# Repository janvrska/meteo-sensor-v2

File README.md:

# Meteo sensor v2
## Custom PCB project of LoraWAN weather sensor

<div>

</div>

**Components :**
 - [Atmel ATMega3208](https://cz.mouser.com/ProductDetail/Microchip-Technology-Atmel/ATMEGA3208-AFR?qs=y6ZabgHbY%252ByqMua8ssBYRQ==) 
 - [Lora E5 SoC](https://cz.mouser.com/ProductDetail/Seeed-Studio/317990687?qs=hd1VzrDQEGhZOj13wvzSLA==)
 - [Sensirion SHT41](https://cz.mouser.com/ProductDetail/Sensirion/SHT41-AD1B-R2?qs=XAiT9M5g4x92rdly9nbdGg==)
 - [IPX connector](https://cz.mouser.com/ProductDetail/Amphenol-RF/A-1JB?qs=ncxkyCpAYDBidtvTkuzl1Q==)
 - 100 nF capacitors
 - 10 uF capacitors
 - 10k Ω resistors
 - 22 Ω resistors
 - pin headers for debugging, flashing

**Software:**
 - [MegaCoreX](https://github.com/MCUdude/MegaCoreX) - environment for Arduino compatibility  (Serial, Wire, Interrupts)
 - [Sensirion I2C SHT4X library](https://github.com/Sensirion/arduino-i2c-sht4x) -  SHT41 sensor data reading
 - [Platformio](https://platformio.org/)  - development, flashing ATMega

This project assumes, that credentials were configured by Serial [Lora E5 AT Commands](https://files.seeedstudio.com/products/317990687/res/LoRa-E5%20AT%20Command%20Specification_V1.0%20.pdf) (DevEUI, AppKey) before flashing the project code. 

**Flow:**
 1. Should be in a range of some nearest LoraWAN Gateway (can look on [TTNMapper](https://ttnmapper.org/))
 2. Power on the device with 3.3 V (2x AA or 2x AAA batteries) connected to VCC and GND pins (look at [board schema](https://github.com/janvrska/meteo-sensor-v2/blob/main/main-board/board.pdf), SV1 blue line GND down, red line VCC)
 3. The device will try to OTA join configured LoraWAN network
 4. Broadcast data packet (temperature, humidity, voltage)
 5. 2.5 minutes sleeping (configured for DR5, spread factor 7, make sure to not violate ETSI regulations or TTN fair access policy. Should be [calculated](https://avbentem.github.io/airtime-calculator/ttn/eu868) before use)
 6. Back to step 4.
 ```mermaid
stateDiagram
    [*] --> PowerOn
    PowerOn --> Join
    Join --> Measure
    Measure --> SendPacket
    SendPacket --> Sleep
    Sleep --> Measure
```
 
 **Low power** (250 µA measured in sleep)
 - use AT+DR=DR5 (will work only if a gateway is close or open area without a lot of RF noise)
 - use AT+POWER=2 (same above)
 - other AT commands already used in code

**TTN**

Use this payload [formatter](https://github.com/janvrska/meteo-sensor-v2/blob/main/ttn-payload-formatter.js) for decoding. Weather data can be later processed with some TTN integration options (MQTT, webhooks...) 

From personal testing, the sensor could transmit for 4 months on 2x AA batteries with default settings (DR5, AT+POWER=2)

**Photos of setup:**

Soldered by hand and hot air gun
<div>

</div>

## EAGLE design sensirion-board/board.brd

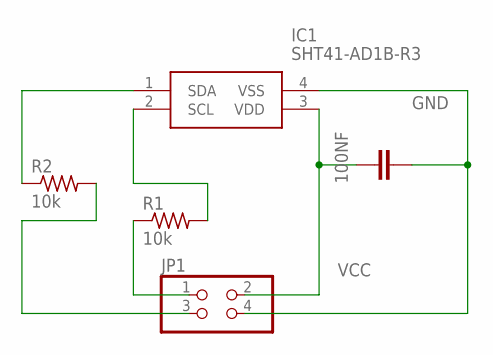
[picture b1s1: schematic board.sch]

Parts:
100NF: 100nF; CAP_0805
IC1: SHT41-AD1B-R3; SHT41AD1BR3
JP1: PINHD-2X2; 2X02
R1, R2: 10k; RES_0805

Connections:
GND: 100NF.2, IC1.4 (VSS), JP1.4
unnamed: JP1.3, R2.2
unnamed: IC1.2 (SCL), R1.2
unnamed: JP1.1, R1.1
unnamed: IC1.1 (SDA), R2.1
VCC: 100NF.1, IC1.3 (VDD), JP1.2

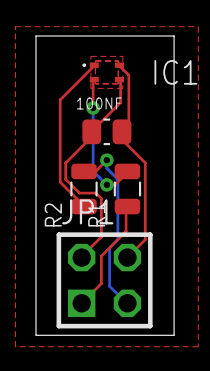
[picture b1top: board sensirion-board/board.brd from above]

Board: 2 copper layers, 7.7 x 16.6 mm, 5 parts (0 on the bottom side), 6 nets.

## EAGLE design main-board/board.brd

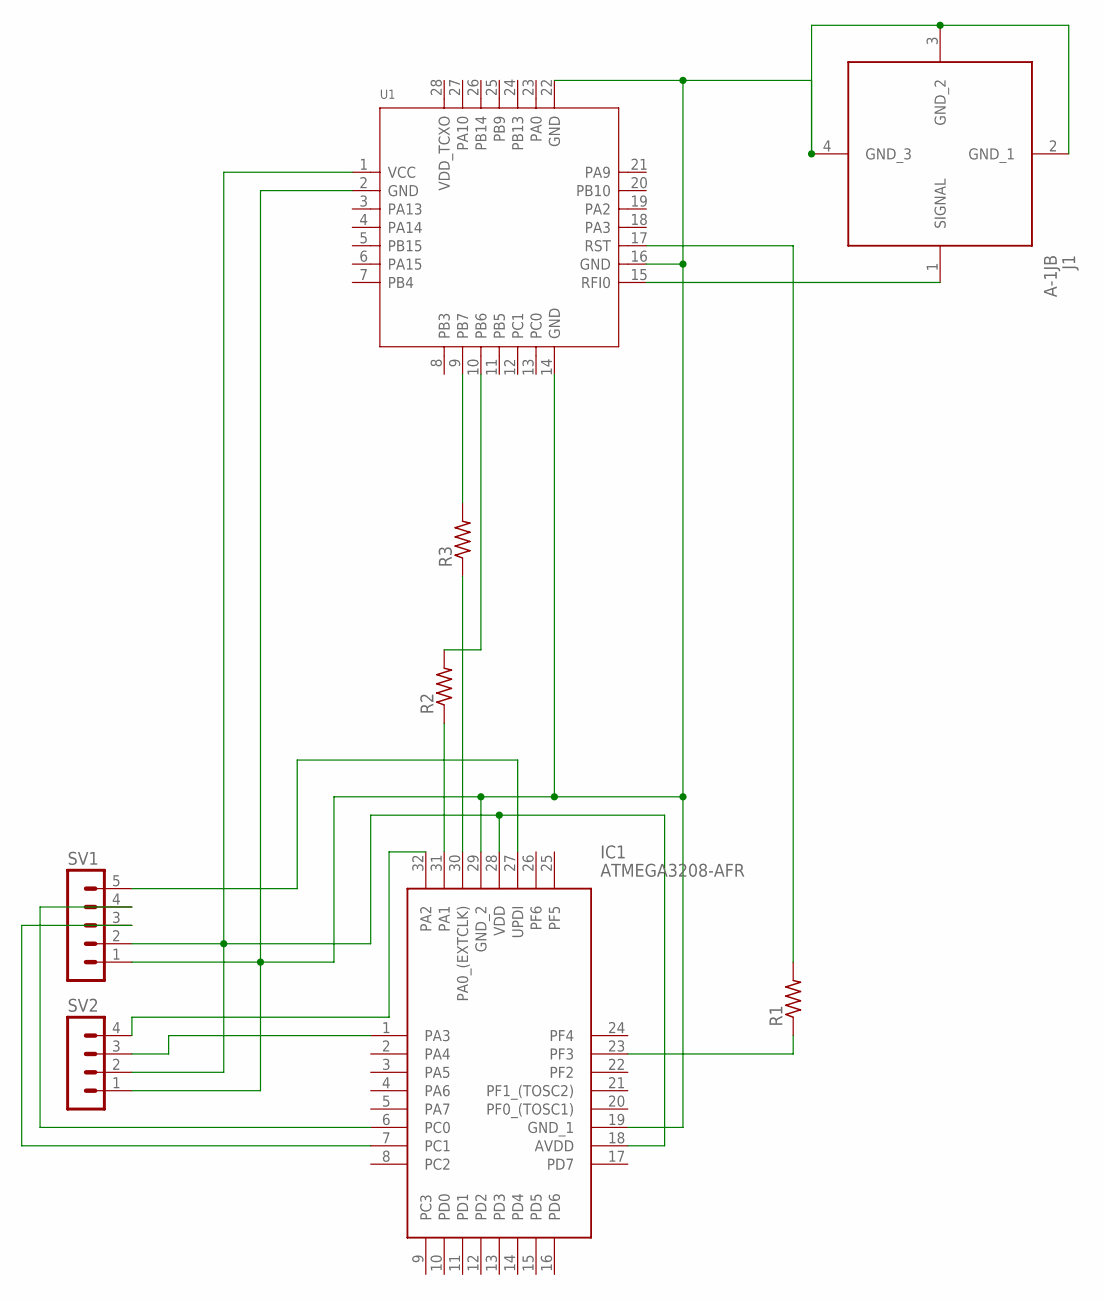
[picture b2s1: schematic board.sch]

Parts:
IC1: ATMEGA3208-AFR; QFP80P900X900X120-32N
J1: A-1JB; A1JB
R1, R2, R3: 22; RES_0805
SV1: MA05-1
SV2: MA04-1
U1: MODULE_LORA_E5; MODULE28P-1.25-12X12X2.5MM

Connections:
unnamed: IC1.19 (GND_1), IC1.29 (GND_2), J1.2 (GND_1), J1.3 (GND_2), J1.4 (GND_3), SV1.1, SV2.1, U1.2 (GND), U1.14 (GND), U1.16 (GND), U1.22 (GND)
unnamed: IC1.27 (UPDI), SV1.5
unnamed: IC1.18 (AVDD), IC1.28 (VDD), SV1.2, SV2.2, U1.1 (VCC)
unnamed: R1.2, U1.17 (RST)
unnamed: J1.1 (SIGNAL), U1.15 (RFI0)
unnamed: R3.2, U1.9 (PB7)
unnamed: R2.2, U1.10 (PB6)
unnamed: IC1.23 (PF3), R1.1
unnamed: IC1.31 (PA1), R2.1
unnamed: IC1.30 (PA0_(EXTCLK)), R3.1
unnamed: IC1.32 (PA2), SV2.4
unnamed: IC1.1 (PA3), SV2.3
unnamed: IC1.6 (PC0), SV1.4
unnamed: IC1.7 (PC1), SV1.3

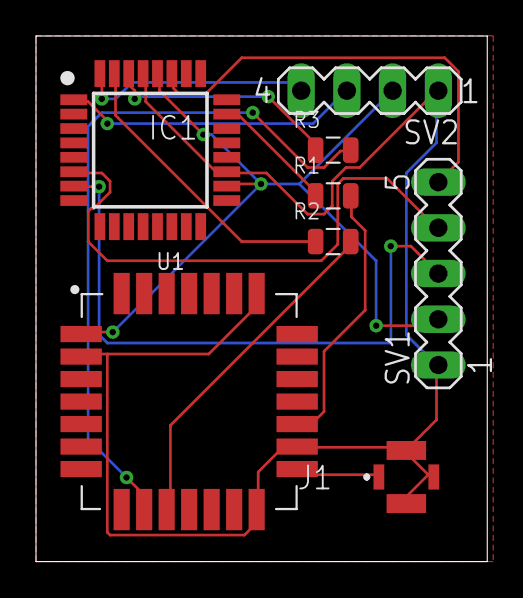
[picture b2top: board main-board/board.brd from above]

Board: 2 copper layers, 25.1 x 29.2 mm, 8 parts (0 on the bottom side), 14 nets.

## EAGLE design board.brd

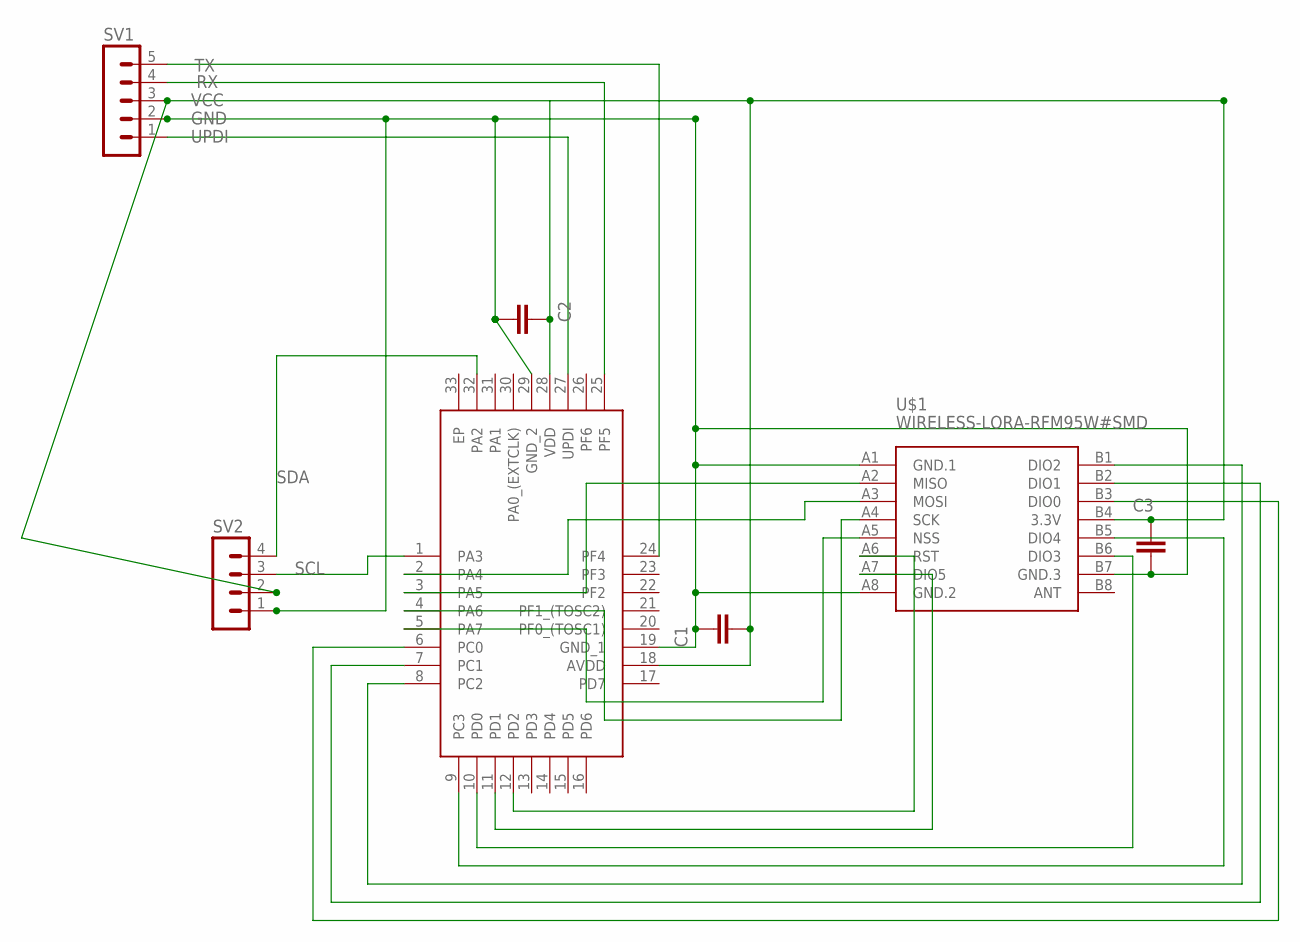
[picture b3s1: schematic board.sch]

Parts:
C1, C2, C3: CC0805KRX7R9BB104; CAP_0805
IC1: ATMEGA3208-MFR; QFN50P500X500X90-33N
SV1: MA05-1
SV2: MA04-1
U$1: WIRELESS-LORA-RFM95W#SMD

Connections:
GND: C1.1, C2.2, C3.2, IC1.19 (GND_1), IC1.29 (GND_2), SV1.2, SV2.1, U$1.A1 (GND.1), U$1.A8 (GND.2), U$1.B7 (GND.3)
unnamed: IC1.2 (PA4), U$1.A3 (MOSI)
unnamed: IC1.3 (PA5), U$1.A2 (MISO)
unnamed: IC1.4 (PA6), U$1.A4 (SCK)
unnamed: IC1.5 (PA7), U$1.A5 (NSS)
unnamed: IC1.11 (PD1), U$1.A7 (DIO5)
unnamed: IC1.12 (PD2), U$1.A6 (RST)
unnamed: IC1.6 (PC0), U$1.B3 (DIO0)
unnamed: IC1.7 (PC1), U$1.B2 (DIO1)
unnamed: IC1.8 (PC2), U$1.B1 (DIO2)
unnamed: IC1.9 (PC3), U$1.B5 (DIO4)
unnamed: IC1.10 (PD0), U$1.B6 (DIO3)
RX: IC1.25 (PF5), SV1.4
SCL: IC1.1 (PA3), SV2.3
SDA: IC1.32 (PA2), SV2.4
TX: IC1.24 (PF4), SV1.5
UPDI: IC1.27 (UPDI), SV1.1
VCC: C1.2, C2.1, C3.1, IC1.18 (AVDD), IC1.28 (VDD), SV1.3, SV2.2, U$1.B4 (3.3V)

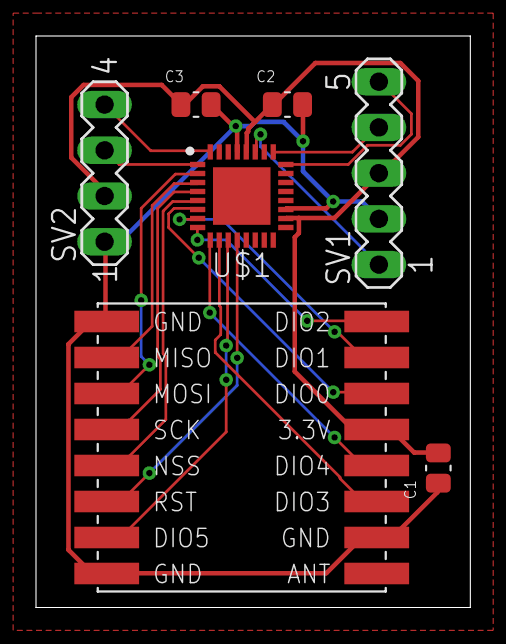
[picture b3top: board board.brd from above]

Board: 2 copper layers, 24.1 x 31.8 mm, 7 parts (0 on the bottom side), 18 nets.

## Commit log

2021-10-24 complete
2022-10-05 project cleanup
2022-10-05 add boards schema
2022-10-05 add ttn payload-formatter
2023-08-14 add power profiles, correct values

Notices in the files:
parts and their libraries:
diy-modules: Released under the Creative Commons Attribution 4.0 International License: http://creativecommons.org/licenses/by/4.0
